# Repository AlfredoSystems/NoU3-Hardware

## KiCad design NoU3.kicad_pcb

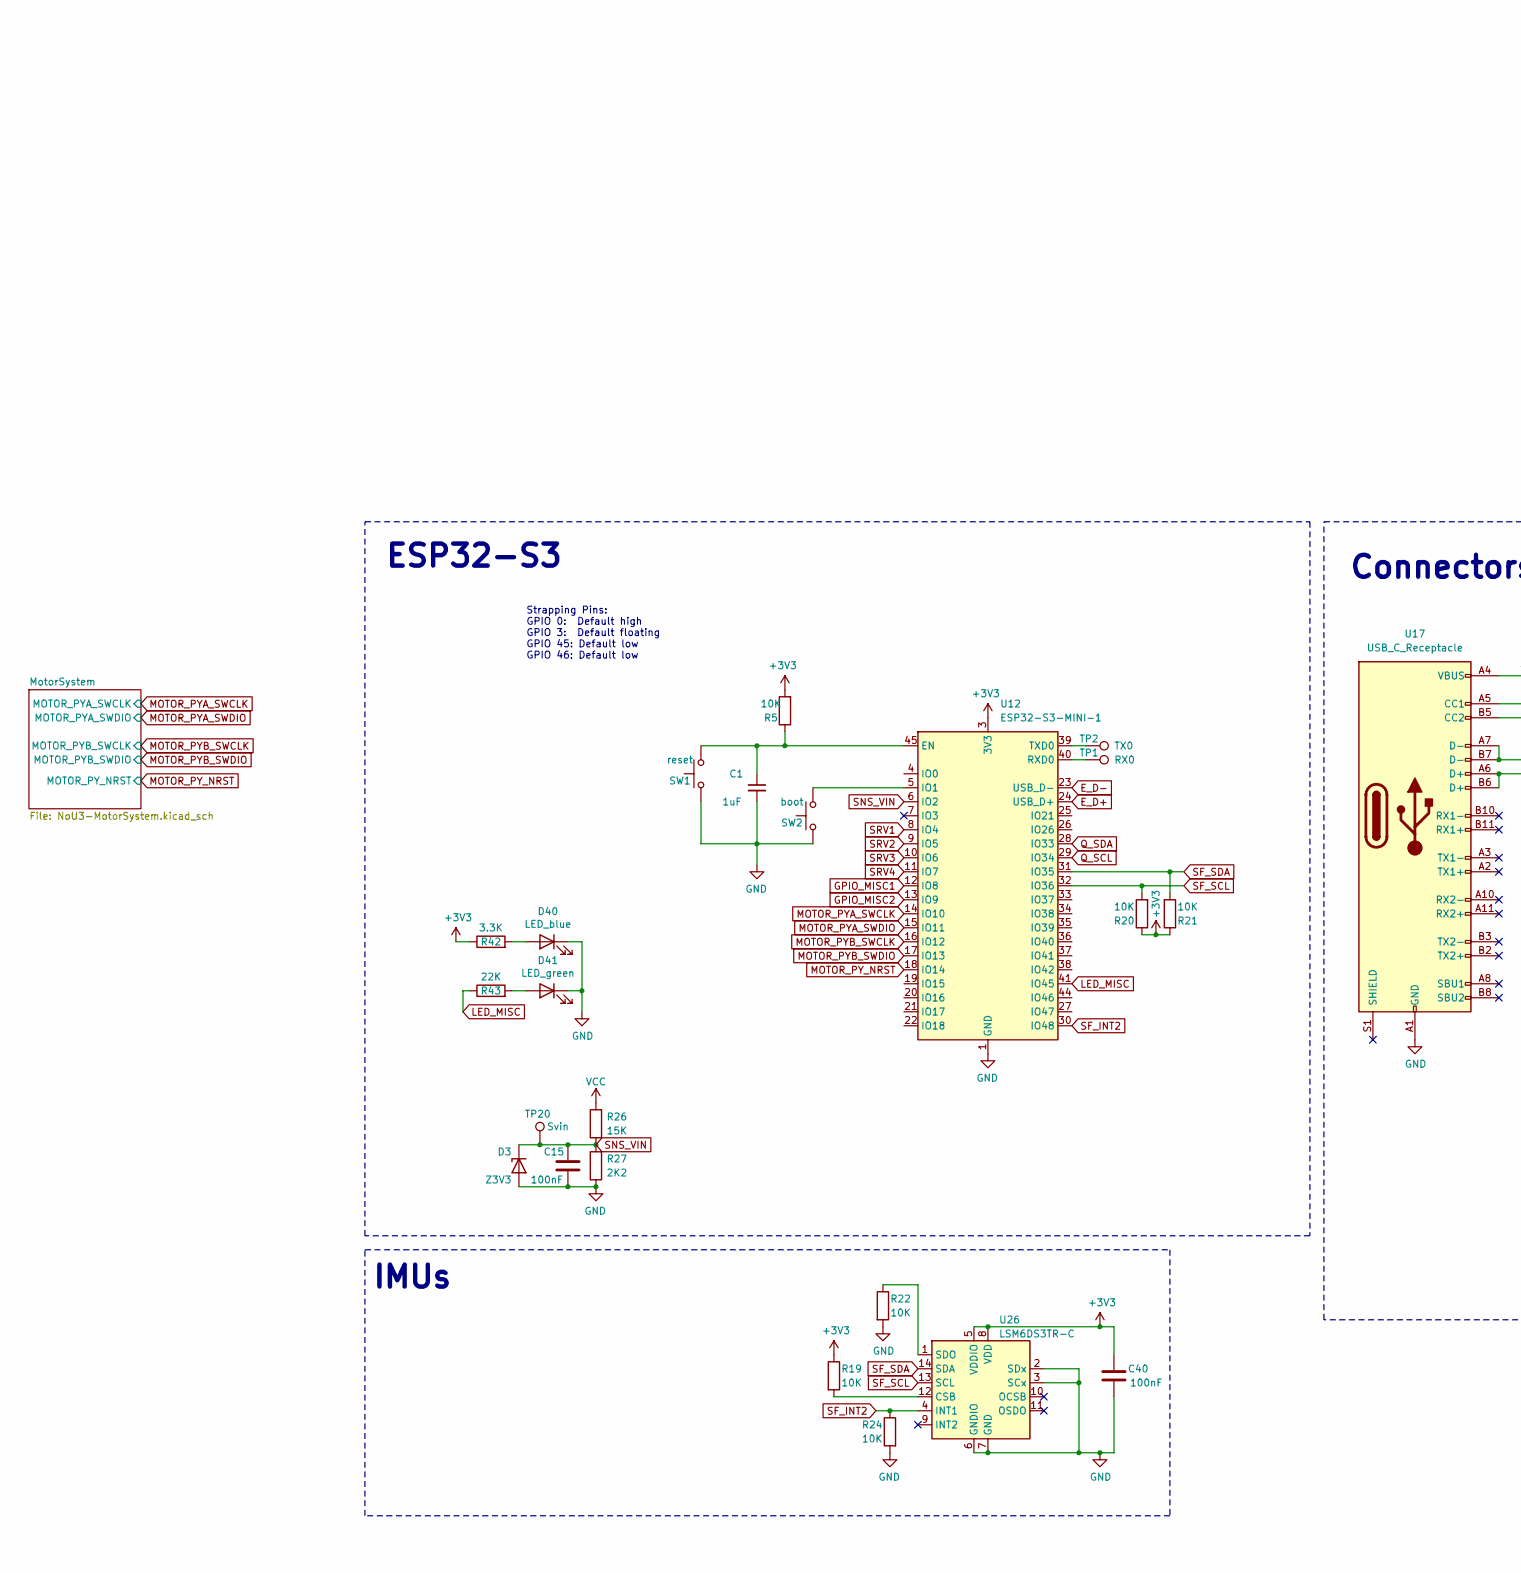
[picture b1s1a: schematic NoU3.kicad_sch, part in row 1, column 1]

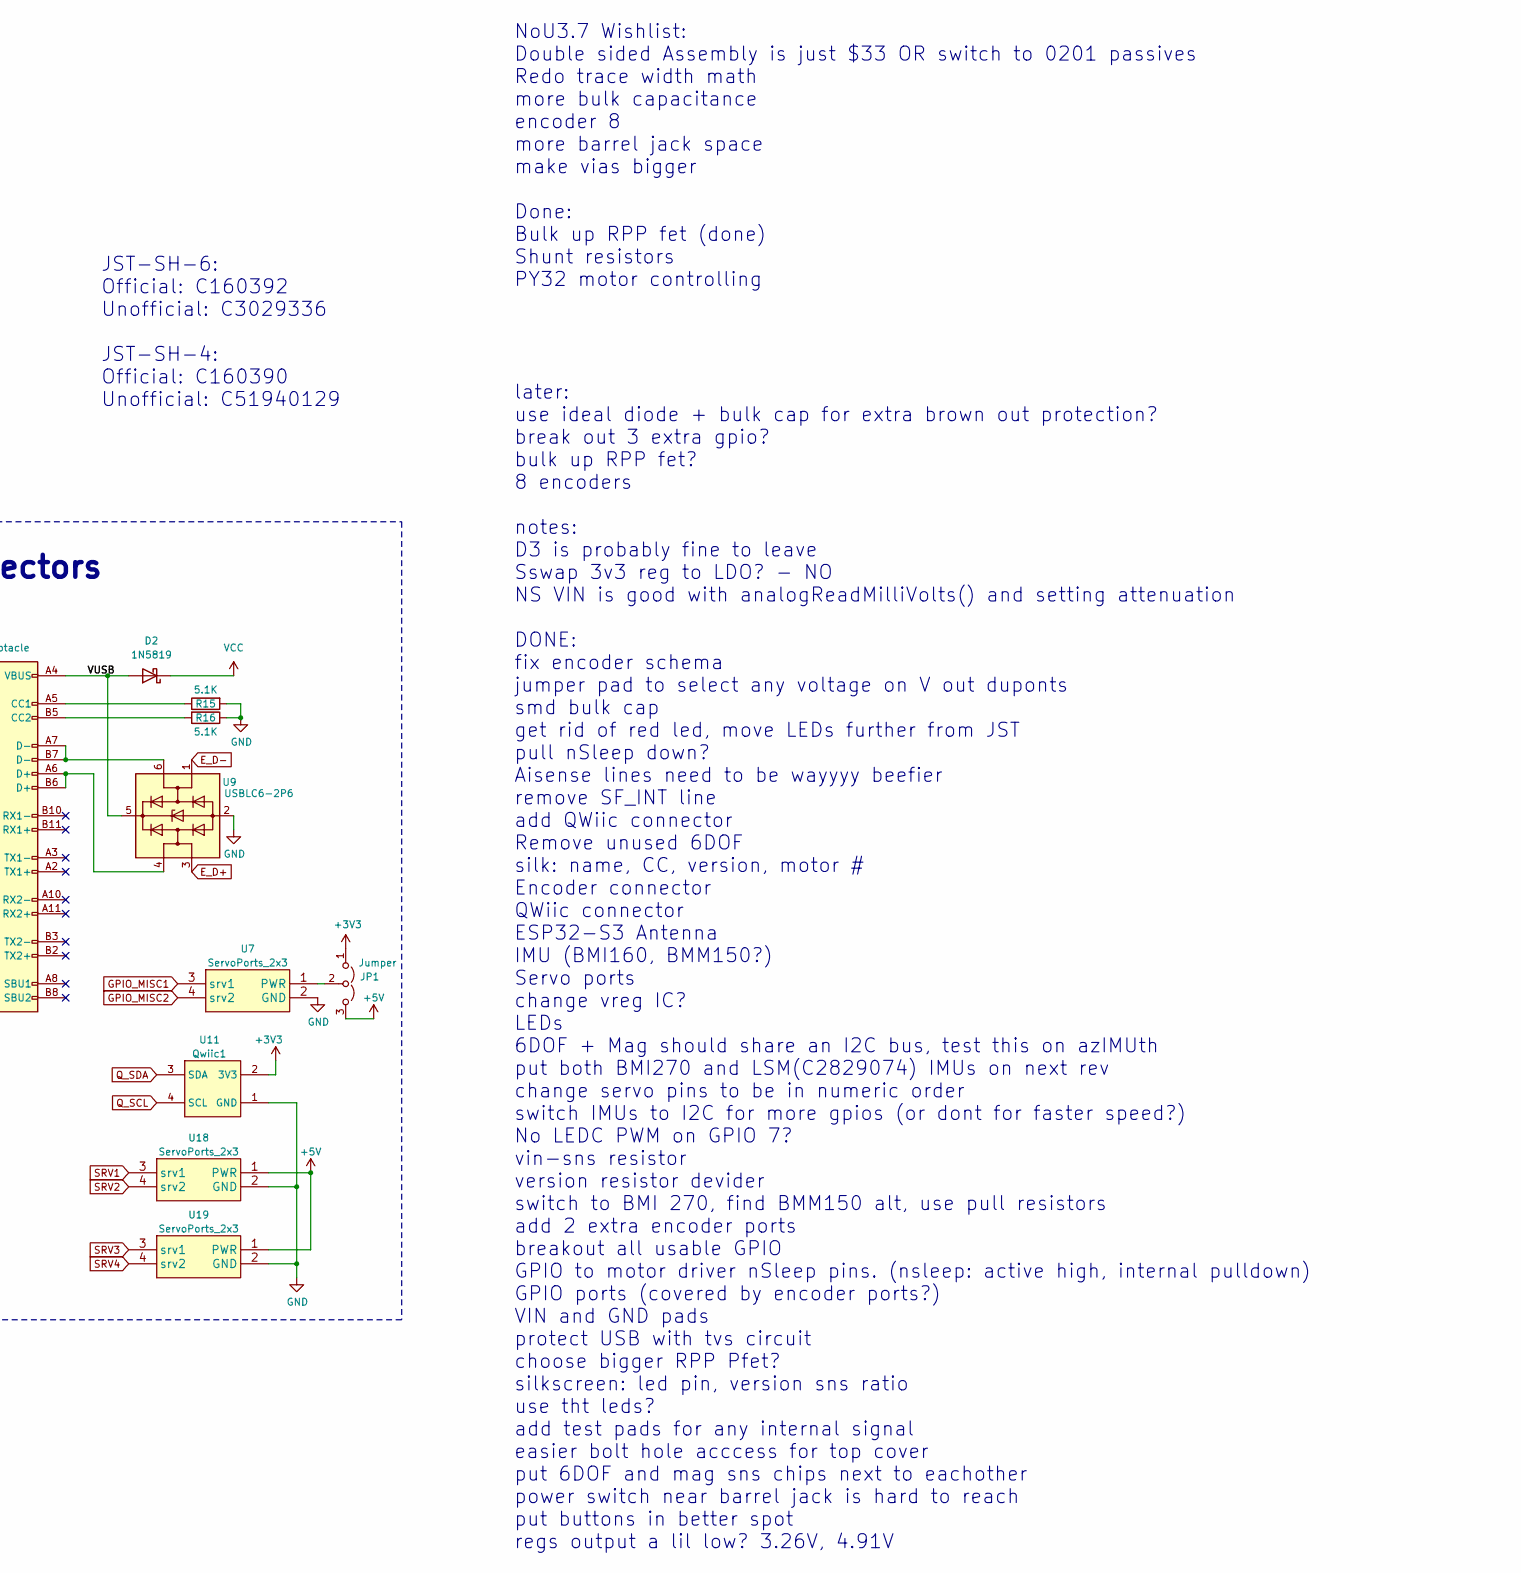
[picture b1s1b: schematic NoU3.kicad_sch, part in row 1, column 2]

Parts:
C1: 1uF; C_0402_1005Metric; LCSC C52923
C15, C40: 100nF; C_0402_1005Metric; LCSC C307331
D2: 1N5819; D_SOD-323; LCSC C191023
D3: Z3V3; D_SOD-323; LCSC C75073
D40: LED_blue; LED_0402_1005Metric; LCSC C130724
D41: LED_green; LED_0402_1005Metric; LCSC C965793
JP1: Jumper; SolderJumper-3-Small
R5, R19, R20, R21, R22, R24: 10K; R_0402_1005Metric; LCSC C25744
R15, R16: 5.1K; R_0402_1005Metric; LCSC C25905
R26: 15K; R_0402_1005Metric; LCSC C25756
R27: 2K2; R_0402_1005Metric; LCSC C25879
R42: 3.3K; R_0402_1005Metric
R43: 22K; R_0402_1005Metric
SW1: reset; Button_SKRKAEE020; LCSC C115357
SW2: boot; Button_SKRKAEE020; LCSC C115357
TP1: RX0; PogoPad1
TP2: TX0; PogoPad1
TP20: Svin; PogoPad1
U7, U18, U19: ServoPorts_2x3; LCSC C5116479
U9: USBLC6-2P6; SOT-666; LCSC C2827693
U11: Qwiic1; JST_SH_BM04B-SRSS-TB_1x04-1MP_P1.00mm_Vertical; LCSC C51940129
U12: ESP32-S3-MINI-1; ESP32-S2-MINI-1; LCSC C2913206
U17: USB_C_Receptacle; USB_TYPE-C-31-M-12; LCSC C165948
U26: LSM6DS3TR-C; Bosch_LGA-14_3x2.5mm_P0.5mm; LCSC C967633

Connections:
+3V3: C40.1, JP1.1 (A), R5.2, R19.1, R20.1, R21.1, R42.1, U11.2 (3V3), U12.3 (3V3), U26.5 (VDDIO), U26.8 (VDD); also elsewhere on the board
+5V: JP1.3 (B), U18.1 (PWR), U19.1 (PWR); also elsewhere on the board
/VUSB: D2.2 (A), U9.5 (VBUS), U17.A4 (VBUS), U17.A9 (VBUS), U17.B4 (VBUS), U17.B9 (VBUS)
E_D+: U9.3 (I/O2), U12.24 (USB_D+)
E_D-: U9.1 (I/O1), U12.23 (USB_D-)
GND: C1.2, C15.2, C40.2, D3.2 (A), D40.1 (K), D41.1 (K), R15.2, R16.1, R22.2, R24.2, R27.1, SW1.2, SW2.2, U7.2 (GND), U9.2 (GND), U11.1 (GND), U12.1 (GND), U12.2 (GND), U12.42 (GND), U12.43 (GND), U12.46 (GND), U12.47 (GND), U12.48 (GND), U12.49 (GND), U12.50 (GND), U12.51 (GND), U12.52 (GND), U12.53 (GND), U12.54 (GND), U12.55 (GND), U12.56 (GND), U12.57 (GND), U12.58 (GND), U12.59 (GND), U12.60 (GND), U12.61 (GND), U12.62 (GND), U12.63 (GND), U12.64 (GND), U12.65 (GND), U17.A1 (GND), U17.A12 (GND), U17.B1 (GND), U17.B12 (GND), U18.2 (GND), U19.2 (GND), U26.2 (SDx), U26.3 (SCx), U26.6 (GNDIO), U26.7 (GND); also elsewhere on the board
GPIO_MISC1: U7.3 (srv1), U12.12 (IO8)
GPIO_MISC2: U7.4 (srv2), U12.13 (IO9)
LED_MISC: R43.1, U12.41 (IO45)
MOTOR_PYA_SWCLK: U12.14 (IO10); also elsewhere on the board
MOTOR_PYA_SWDIO: U12.15 (IO11); also elsewhere on the board
MOTOR_PYB_SWCLK: U12.16 (IO12); also elsewhere on the board
MOTOR_PYB_SWDIO: U12.17 (IO13); also elsewhere on the board
MOTOR_PY_NRST: U12.18 (IO14); also elsewhere on the board
unnamed: D40.2 (A), R42.2
unnamed: D41.2 (A), R43.2
unnamed: JP1.2 (C), U7.1 (PWR)
unnamed: C1.1, R5.1, SW1.1, U12.45 (EN)
unnamed: SW2.1, U12.5 (IO1)
unnamed: TP1.1 (1_1), U12.40 (RXD0)
unnamed: TP2.1 (1_1), U12.39 (TXD0)
unnamed: R15.1, U17.A5 (CC1)
unnamed: R16.2, U17.B5 (CC2)
unnamed: U9.4 (I/O2), U17.A6 (D+), U17.B6 (D+)
unnamed: U9.6 (I/O1), U17.A7 (D-), U17.B7 (D-)
unnamed: R19.2, U26.12 (CSB)
unnamed: R22.1, U26.1 (SDO)
Q_SCL: U11.4 (SCL), U12.29 (IO34)
Q_SDA: U11.3 (SDA), U12.28 (IO33)
SF_INT2: R24.1, U12.30 (IO48), U26.4 (INT1)
SF_SCL: R20.2, U12.32 (IO36), U26.13 (SCL)
SF_SDA: R21.2, U12.31 (IO35), U26.14 (SDA)
SNS_VIN: C15.1, D3.1 (K), R26.1, R27.2, TP20.1 (1_1), U12.6 (IO2)
SRV1: U12.8 (IO4), U18.3 (srv1)
SRV2: U12.9 (IO5), U18.4 (srv2)
SRV3: U12.10 (IO6), U19.3 (srv1)
SRV4: U12.11 (IO7), U19.4 (srv2)
VCC: D2.1 (K), R26.2; also elsewhere on the board

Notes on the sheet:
IMUs
Strapping Pins: GPIO 0: Default high GPIO 3: Default floating GPIO 45: Default low GPIO 46: Default low
NoU3.7 Wishlist: Double sided Assembly is just $33 OR switch to 0201 passives Redo trace width math more bulk capacitance encoder 8 more barrel jack space make vias bigger Done: Bulk up RPP fet (done) Shunt resistors PY32 motor controlling later: use ideal diode + bulk cap for extra brown out prote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
Connectors
ESP32-S3
JST-SH-6: Official: C160392 Unofficial: C3029336 JST-SH-4: Official: C160390 Unofficial: C51940129

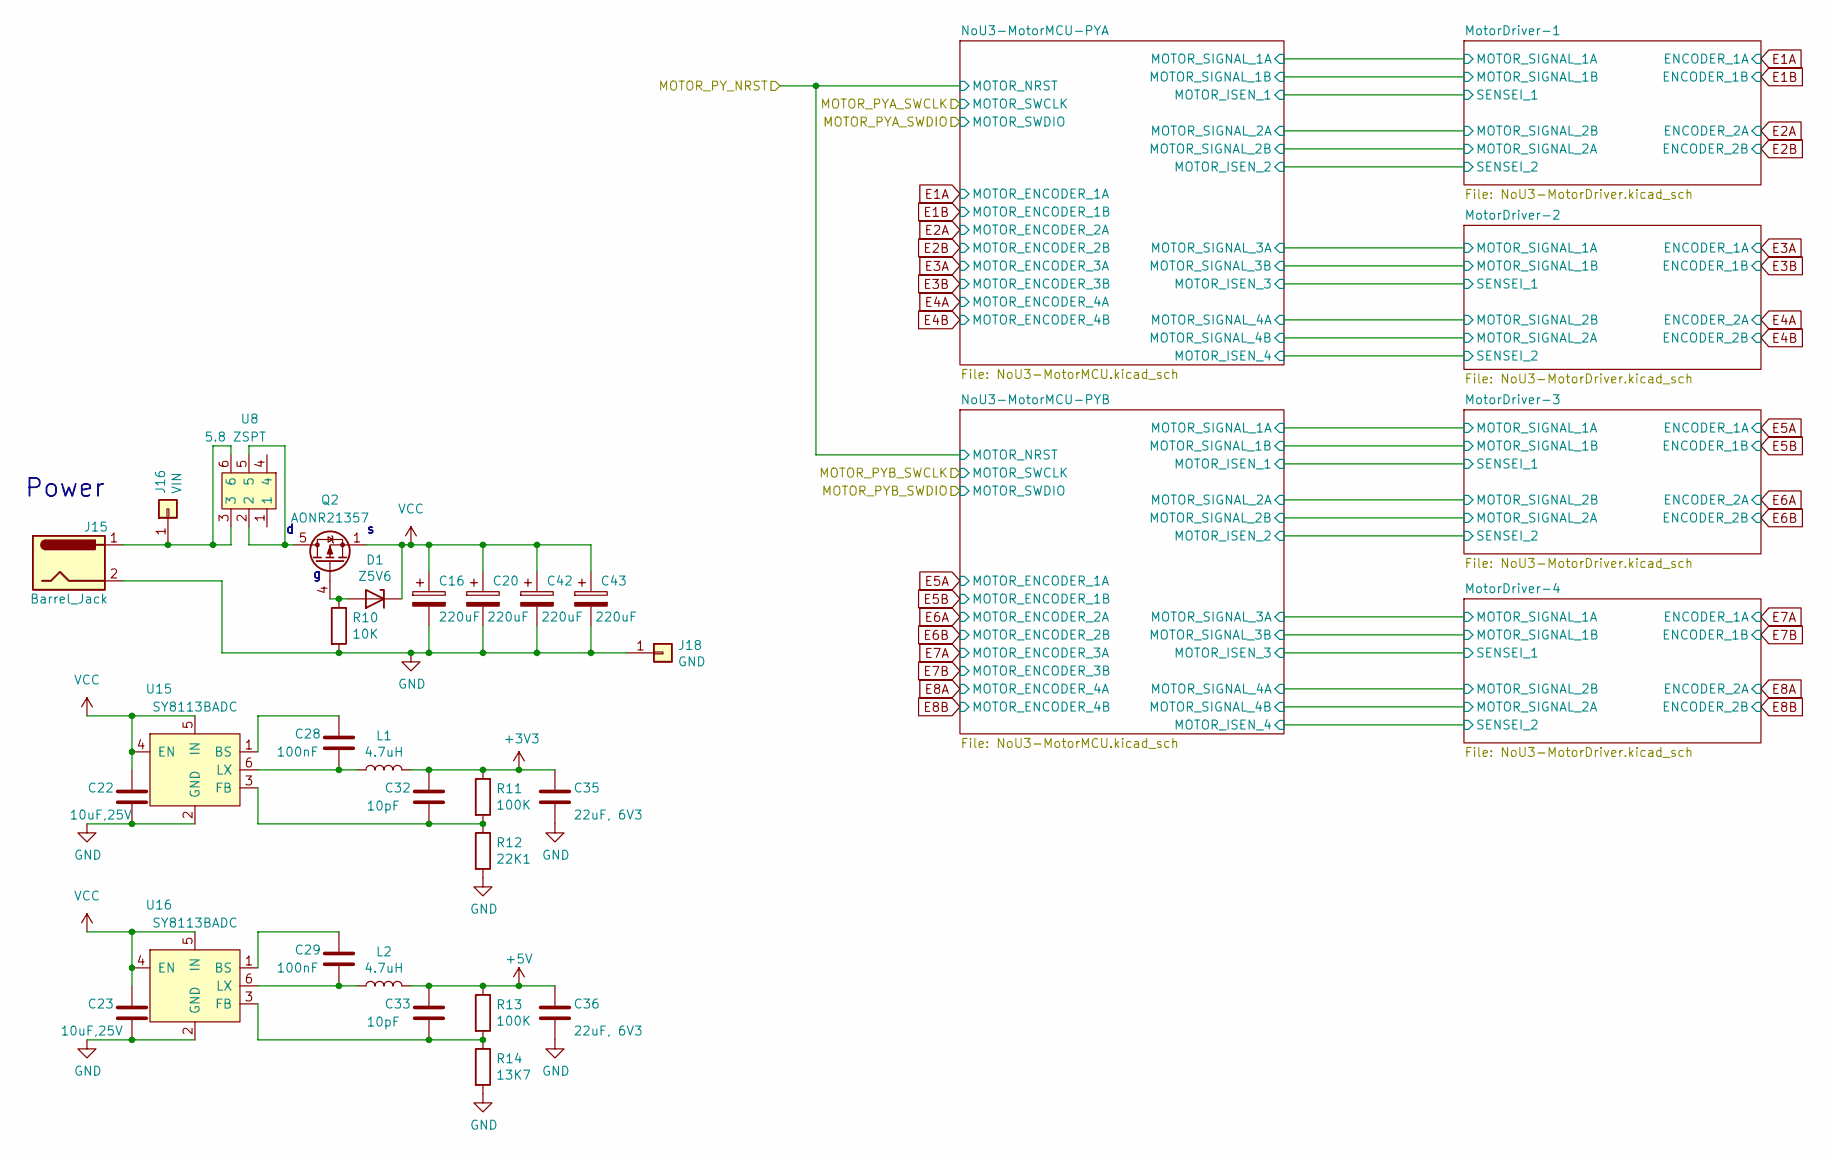
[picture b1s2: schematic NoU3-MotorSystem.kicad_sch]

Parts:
C16, C20, C42, C43: 220uF; CP_Elec_6.3x7.7_slim; LCSC C4747974
C22, C23: 10uF,25V; C_0603_1608Metric; LCSC C96446
C28, C29: 100nF; C_0402_1005Metric; LCSC C307331
C32, C33: 10pF; C_0402_1005Metric; LCSC C32949
C35, C36: 22uF, 6V3; C_0603_1608Metric; LCSC C59461
D1: Z5V6; D_SOD-323; LCSC C22612
J15: Barrel_Jack; DC-005C_1; LCSC C84007
J16: VIN; PinSocket_1x01_P2.54mm_Vertical
J18: GND; PinSocket_1x01_P2.54mm_Vertical
L1, L2: 4.7uH; LVF252A12; LCSC C88528
Q2: AONR21357; DFN-8-1EP_3x3mm_P0.65mm_EP1.55x2.4mm; LCSC C431196
R10: 10K; R_0402_1005Metric; LCSC C25744
R11, R13: 100K; R_0402_1005Metric; LCSC C25741
R12: 22K1; R_0402_1005Metric; LCSC C163478
R14: 13K7; R_0402_1005Metric; LCSC C25854
U8: 5.8 ZSPT; XKB5858-Z-75; LCSC C963201
U15, U16: SY8113BADC; TSOT-23-6; LCSC C78989

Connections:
+3V3: C32.1, C35.1, L1.2, R11.1; also elsewhere on the board
+5V: C33.1, C36.1, L2.2, R13.1; also elsewhere on the board
GND: C16.2, C20.2, C22.2, C23.2, C35.2, C36.2, C42.2, C43.2, J15.2, J18.1 (Pin_1_1), R10.2, R12.2, R14.2, U15.2 (GND), U16.2 (GND); also elsewhere on the board
unnamed: D1.2 (A), Q2.4 (G), R10.1
unnamed: J15.1, J16.1 (Pin_1_1), U8.3, U8.6
unnamed: Q2.5 (D), Q2.6 (D), Q2.7 (D), Q2.8 (D), Q2.9 (D), U8.2, U8.5
unnamed: C28.1, U15.1 (BS)
unnamed: C32.2, R11.2, R12.1, U15.3 (FB)
unnamed: C28.2, L1.1, U15.6 (LX)
unnamed: C29.1, U16.1 (BS)
unnamed: C33.2, R13.2, R14.1, U16.3 (FB)
unnamed: C29.2, L2.1, U16.6 (LX)
VCC: C16.1, C20.1, C22.1, C23.1, C42.1, C43.1, D1.1 (K), Q2.1 (S), Q2.2 (S), Q2.3 (S), U15.4 (EN), U15.5 (IN), U16.4 (EN), U16.5 (IN); also elsewhere on the board

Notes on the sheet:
Power

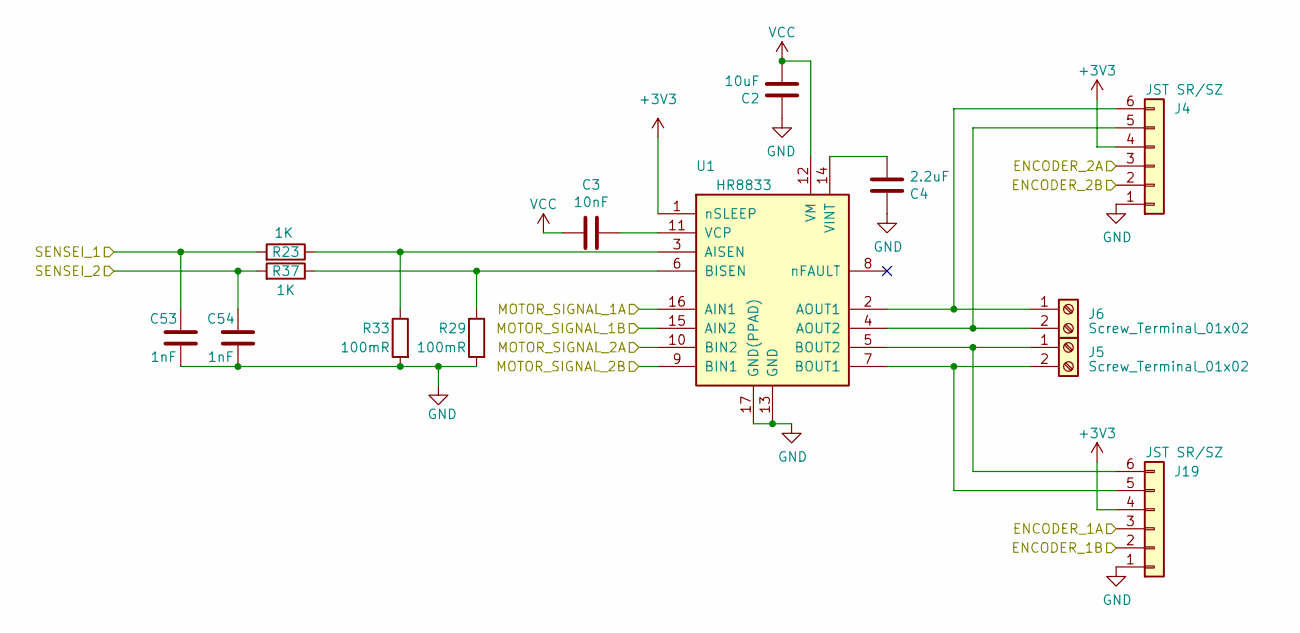
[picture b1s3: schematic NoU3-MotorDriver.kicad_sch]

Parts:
C2: 10uF; C_0805_2012Metric; LCSC C15850
C3: 10nF; C_0402_1005Metric; LCSC C15195
C4: 2.2uF; C_0402_1005Metric; LCSC C12530
C53, C54: 1nF; C_0402_1005Metric; LCSC C1523
J4, J19: JST SR/SZ; JST_SH_1x06_Vertical; LCSC C3029336
J5, J6: Screw_Terminal_01x02; TerminalBlock_Ningbo_2P_5mm; LCSC C557646
R23, R37: 1K; R_0402_1005Metric; LCSC C11702
R29, R33: 100mR; R_0805_2012Metric; LCSC C327057
U1: HR8833; HR8833-0.6mm; LCSC C128666

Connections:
+3V3: J4.4, J19.4, U1.1 (nSLEEP); also elsewhere on the board
/MotorSystem/MotorDriver-1/MOTOR_SIGNAL_1A: U1.16 (AIN1); also elsewhere on the board
/MotorSystem/MotorDriver-1/MOTOR_SIGNAL_1B: U1.15 (AIN2); also elsewhere on the board
/MotorSystem/MotorDriver-1/MOTOR_SIGNAL_2A: U1.10 (BIN2); also elsewhere on the board
/MotorSystem/MotorDriver-1/MOTOR_SIGNAL_2B: U1.9 (BIN1); also elsewhere on the board
/MotorSystem/MotorDriver-1/SENSEI_1: C53.1, R23.2; also elsewhere on the board
/MotorSystem/MotorDriver-1/SENSEI_2: C54.1, R37.2; also elsewhere on the board
E1A: J19.3; also elsewhere on the board
E1B: J19.2; also elsewhere on the board
E2A: J4.3; also elsewhere on the board
E2B: J4.2; also elsewhere on the board
GND: C2.2, C4.2, C53.2, C54.2, J4.1, J19.1, R29.2, R33.2, U1.13 (GND), U1.17 (GND(PPAD)); also elsewhere on the board
unnamed: J4.5, J6.2, U1.4 (AOUT2)
unnamed: J4.6, J6.1, U1.2 (AOUT1)
unnamed: J5.2, J19.5, U1.7 (BOUT1)
unnamed: J5.1, J19.6, U1.5 (BOUT2)
unnamed: R23.1, R33.1, U1.3 (AISEN)
unnamed: R29.1, R37.1, U1.6 (BISEN)
unnamed: C3.2, U1.11 (VCP)
unnamed: C4.1, U1.14 (VINT)
VCC: C2.1, C3.1, U1.12 (VM); also elsewhere on the board

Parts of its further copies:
C5, C8, C11: 10uF; C_0805_2012Metric; LCSC C15850
C6, C9, C12: 10nF; C_0402_1005Metric; LCSC C15195
C7, C10, C13: 2.2uF; C_0402_1005Metric; LCSC C12530
C49, C50, C55, C56, C59, C60: 1nF; C_0402_1005Metric; LCSC C1523
J1, J7, J10, J13, J17, J20: JST SR/SZ; JST_SH_1x06_Vertical; LCSC C3029336
J2, J3, J8, J9, J11, J12: Screw_Terminal_01x02; TerminalBlock_Ningbo_2P_5mm; LCSC C557646
R30, R31, R32, R34, R35, R36: 100mR; R_0805_2012Metric; LCSC C327057
R40, R41, R44, R45, R48, R49: 1K; R_0402_1005Metric; LCSC C11702
U4, U5, U6: HR8833; HR8833-0.6mm; LCSC C128666

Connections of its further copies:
+3V3: J1.4, J7.4, J10.4, J13.4, J17.4, J20.4, U4.1 (nSLEEP), U5.1 (nSLEEP), U6.1 (nSLEEP); also elsewhere on the board
/MotorSystem/MotorDriver-2/MOTOR_SIGNAL_1A: U4.16 (AIN1); also elsewhere on the board
/MotorSystem/MotorDriver-2/MOTOR_SIGNAL_1B: U4.15 (AIN2); also elsewhere on the board
/MotorSystem/MotorDriver-2/MOTOR_SIGNAL_2A: U4.10 (BIN2); also elsewhere on the board
/MotorSystem/MotorDriver-2/MOTOR_SIGNAL_2B: U4.9 (BIN1); also elsewhere on the board
/MotorSystem/MotorDriver-2/SENSEI_1: C55.1, R40.2; also elsewhere on the board
/MotorSystem/MotorDriver-2/SENSEI_2: C56.1, R41.2; also elsewhere on the board
/MotorSystem/MotorDriver-3/MOTOR_SIGNAL_1A: U5.16 (AIN1); also elsewhere on the board
/MotorSystem/MotorDriver-3/MOTOR_SIGNAL_1B: U5.15 (AIN2); also elsewhere on the board
/MotorSystem/MotorDriver-3/MOTOR_SIGNAL_2A: U5.10 (BIN2); also elsewhere on the board
/MotorSystem/MotorDriver-3/MOTOR_SIGNAL_2B: U5.9 (BIN1); also elsewhere on the board
/MotorSystem/MotorDriver-3/SENSEI_1: C49.1, R44.2; also elsewhere on the board
/MotorSystem/MotorDriver-3/SENSEI_2: C50.1, R45.2; also elsewhere on the board
/MotorSystem/MotorDriver-4/MOTOR_SIGNAL_1A: U6.16 (AIN1); also elsewhere on the board
/MotorSystem/MotorDriver-4/MOTOR_SIGNAL_1B: U6.15 (AIN2); also elsewhere on the board
/MotorSystem/MotorDriver-4/MOTOR_SIGNAL_2A: U6.10 (BIN2); also elsewhere on the board
/MotorSystem/MotorDriver-4/MOTOR_SIGNAL_2B: U6.9 (BIN1); also elsewhere on the board
/MotorSystem/MotorDriver-4/SENSEI_1: C59.1, R48.2; also elsewhere on the board
/MotorSystem/MotorDriver-4/SENSEI_2: C60.1, R49.2; also elsewhere on the board
E3A: J7.3; also elsewhere on the board
E3B: J7.2; also elsewhere on the board
E4A: J13.3; also elsewhere on the board
E4B: J13.2; also elsewhere on the board
E5A: J10.3; also elsewhere on the board
E5B: J10.2; also elsewhere on the board
E6A: J17.3; also elsewhere on the board
E6B: J17.2; also elsewhere on the board
E7A: J1.3; also elsewhere on the board
E7B: J1.2; also elsewhere on the board
E8A: J20.3; also elsewhere on the board
E8B: J20.2; also elsewhere on the board
GND: C5.2, C7.2, C8.2, C10.2, C11.2, C13.2, C49.2, C50.2, C55.2, C56.2, C59.2, C60.2, J1.1, J7.1, J10.1, J13.1, J17.1, J20.1, R30.2, R31.2, R32.2, R34.2, R35.2, R36.2, U4.13 (GND), U4.17 (GND(PPAD)), U5.13 (GND), U5.17 (GND(PPAD)), U6.13 (GND), U6.17 (GND(PPAD)); also elsewhere on the board
unnamed: J1.5, J2.2, U6.7 (BOUT1)
unnamed: J1.6, J2.1, U6.5 (BOUT2)
unnamed: J7.5, J8.2, U4.7 (BOUT1)
unnamed: J7.6, J8.1, U4.5 (BOUT2)
unnamed: J10.5, J11.2, U5.7 (BOUT1)
unnamed: J10.6, J11.1, U5.5 (BOUT2)
unnamed: J12.1, J17.6, U5.2 (AOUT1)
unnamed: J12.2, J17.5, U5.4 (AOUT2)
unnamed: J9.2, J13.5, U4.4 (AOUT2)
unnamed: J9.1, J13.6, U4.2 (AOUT1)
unnamed: J3.2, J20.5, U6.4 (AOUT2)
unnamed: J3.1, J20.6, U6.2 (AOUT1)
unnamed: R34.1, R40.1, U4.3 (AISEN)
unnamed: R30.1, R41.1, U4.6 (BISEN)
unnamed: C6.2, U4.11 (VCP)
unnamed: C7.1, U4.14 (VINT)
unnamed: R35.1, R44.1, U5.3 (AISEN)
unnamed: R31.1, R45.1, U5.6 (BISEN)
unnamed: C9.2, U5.11 (VCP)
unnamed: C10.1, U5.14 (VINT)
unnamed: R36.1, R48.1, U6.3 (AISEN)
unnamed: R32.1, R49.1, U6.6 (BISEN)
unnamed: C12.2, U6.11 (VCP)
unnamed: C13.1, U6.14 (VINT)
VCC: C5.1, C6.1, C8.1, C9.1, C11.1, C12.1, U4.12 (VM), U5.12 (VM), U6.12 (VM); also elsewhere on the board

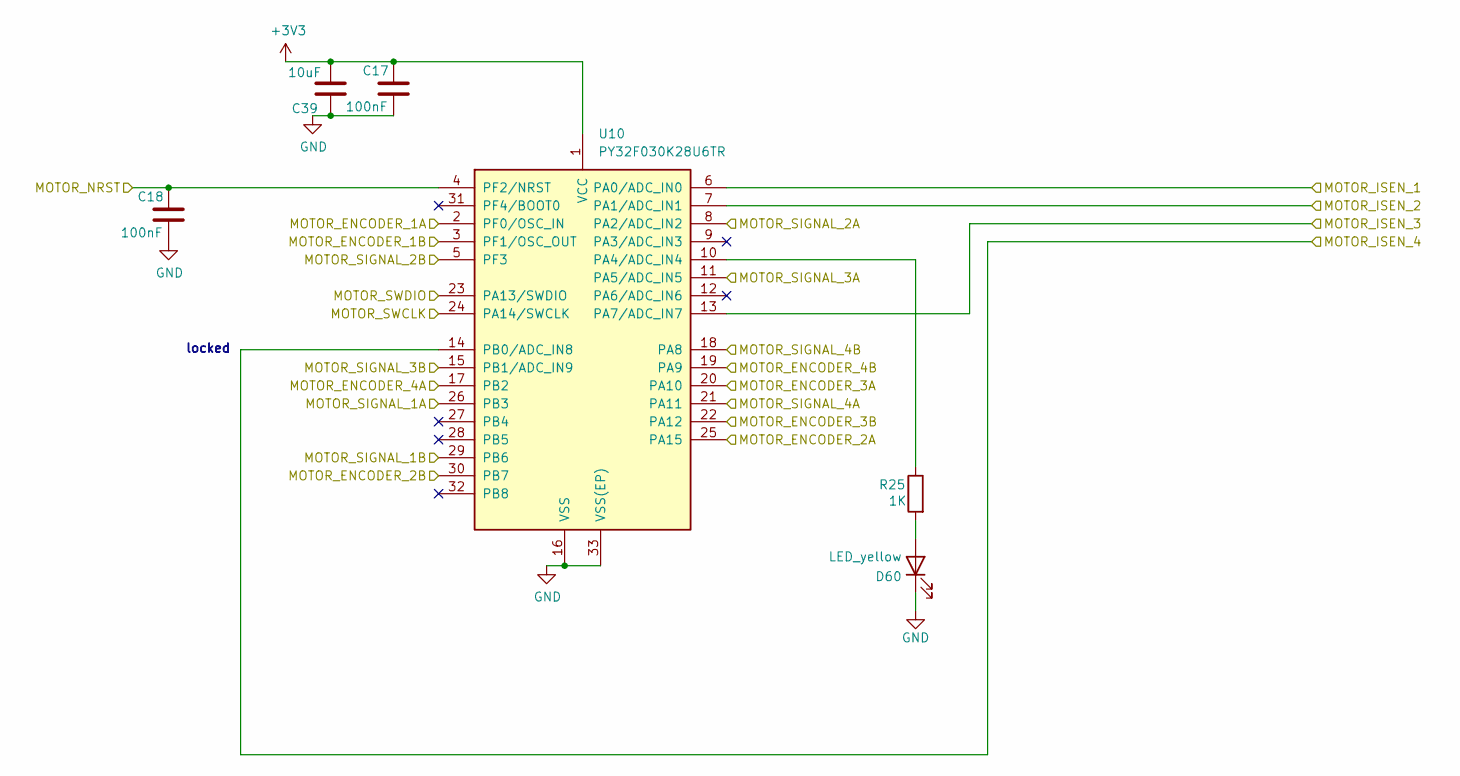
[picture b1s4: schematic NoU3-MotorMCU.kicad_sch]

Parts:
C17, C18: 100nF; C_0402_1005Metric; LCSC C307331
C39: 10uF; C_0402_1005Metric; LCSC C15525
D60: LED_yellow; LED_0402_1005Metric; LCSC C130721
R25: 1K; R_0402_1005Metric; LCSC C11702
U10: PY32F030K28U6TR; VQFN-32-1EP_5x5mm_P0.5mm_EP3.5x3.5mm; LCSC C3018718

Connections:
+3V3: C17.1, C39.2, U10.1 (VCC); also elsewhere on the board
/MotorSystem/MotorDriver-1/MOTOR_SIGNAL_1A: U10.26 (PB3); also elsewhere on the board
/MotorSystem/MotorDriver-1/MOTOR_SIGNAL_1B: U10.29 (PB6); also elsewhere on the board
/MotorSystem/MotorDriver-1/MOTOR_SIGNAL_2A: U10.5 (PF3); also elsewhere on the board
/MotorSystem/MotorDriver-1/MOTOR_SIGNAL_2B: U10.8 (PA2/ADC_IN2); also elsewhere on the board
/MotorSystem/MotorDriver-1/SENSEI_1: U10.6 (PA0/ADC_IN0); also elsewhere on the board
/MotorSystem/MotorDriver-1/SENSEI_2: U10.7 (PA1/ADC_IN1); also elsewhere on the board
/MotorSystem/MotorDriver-2/MOTOR_SIGNAL_1A: U10.11 (PA5/ADC_IN5); also elsewhere on the board
/MotorSystem/MotorDriver-2/MOTOR_SIGNAL_1B: U10.15 (PB1/ADC_IN9); also elsewhere on the board
/MotorSystem/MotorDriver-2/MOTOR_SIGNAL_2A: U10.18 (PA8); also elsewhere on the board
/MotorSystem/MotorDriver-2/MOTOR_SIGNAL_2B: U10.21 (PA11); also elsewhere on the board
/MotorSystem/MotorDriver-2/SENSEI_1: U10.13 (PA7/ADC_IN7); also elsewhere on the board
/MotorSystem/MotorDriver-2/SENSEI_2: U10.14 (PB0/ADC_IN8); also elsewhere on the board
E1A: U10.2 (PF0/OSC_IN); also elsewhere on the board
E1B: U10.3 (PF1/OSC_OUT); also elsewhere on the board
E2A: U10.25 (PA15); also elsewhere on the board
E2B: U10.30 (PB7); also elsewhere on the board
E3A: U10.20 (PA10); also elsewhere on the board
E3B: U10.22 (PA12); also elsewhere on the board
E4A: U10.17 (PB2); also elsewhere on the board
E4B: U10.19 (PA9); also elsewhere on the board
GND: C17.2, C18.2, C39.1, D60.1 (K), U10.16 (VSS), U10.33 (VSS(EP)); also elsewhere on the board
MOTOR_PYA_SWCLK: U10.24 (PA14/SWCLK); also elsewhere on the board
MOTOR_PYA_SWDIO: U10.23 (PA13/SWDIO); also elsewhere on the board
MOTOR_PY_NRST: C18.1, U10.4 (PF2/NRST); also elsewhere on the board
unnamed: D60.2 (A), R25.2
unnamed: R25.1, U10.10 (PA4/ADC_IN4)

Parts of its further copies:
C46, C48: 100nF; C_0402_1005Metric; LCSC C307331
C47: 10uF; C_0402_1005Metric; LCSC C15525
D61: LED_yellow; LED_0402_1005Metric; LCSC C130721
R28: 1K; R_0402_1005Metric; LCSC C11702
U14: PY32F030K28U6TR; VQFN-32-1EP_5x5mm_P0.5mm_EP3.5x3.5mm; LCSC C3018718

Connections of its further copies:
+3V3: C47.2, C48.1, U14.1 (VCC); also elsewhere on the board
/MotorSystem/MotorDriver-3/MOTOR_SIGNAL_1A: U14.26 (PB3); also elsewhere on the board
/MotorSystem/MotorDriver-3/MOTOR_SIGNAL_1B: U14.29 (PB6); also elsewhere on the board
/MotorSystem/MotorDriver-3/MOTOR_SIGNAL_2A: U14.5 (PF3); also elsewhere on the board
/MotorSystem/MotorDriver-3/MOTOR_SIGNAL_2B: U14.8 (PA2/ADC_IN2); also elsewhere on the board
/MotorSystem/MotorDriver-3/SENSEI_1: U14.6 (PA0/ADC_IN0); also elsewhere on the board
/MotorSystem/MotorDriver-3/SENSEI_2: U14.7 (PA1/ADC_IN1); also elsewhere on the board
/MotorSystem/MotorDriver-4/MOTOR_SIGNAL_1A: U14.11 (PA5/ADC_IN5); also elsewhere on the board
/MotorSystem/MotorDriver-4/MOTOR_SIGNAL_1B: U14.15 (PB1/ADC_IN9); also elsewhere on the board
/MotorSystem/MotorDriver-4/MOTOR_SIGNAL_2A: U14.18 (PA8); also elsewhere on the board
/MotorSystem/MotorDriver-4/MOTOR_SIGNAL_2B: U14.21 (PA11); also elsewhere on the board
/MotorSystem/MotorDriver-4/SENSEI_1: U14.13 (PA7/ADC_IN7); also elsewhere on the board
/MotorSystem/MotorDriver-4/SENSEI_2: U14.14 (PB0/ADC_IN8); also elsewhere on the board
E5A: U14.2 (PF0/OSC_IN); also elsewhere on the board
E5B: U14.3 (PF1/OSC_OUT); also elsewhere on the board
E6A: U14.25 (PA15); also elsewhere on the board
E6B: U14.30 (PB7); also elsewhere on the board
E7A: U14.20 (PA10); also elsewhere on the board
E7B: U14.22 (PA12); also elsewhere on the board
E8A: U14.17 (PB2); also elsewhere on the board
E8B: U14.19 (PA9); also elsewhere on the board
GND: C46.2, C47.1, C48.2, D61.1 (K), U14.16 (VSS), U14.33 (VSS(EP)); also elsewhere on the board
MOTOR_PYB_SWCLK: U14.24 (PA14/SWCLK); also elsewhere on the board
MOTOR_PYB_SWDIO: U14.23 (PA13/SWDIO); also elsewhere on the board
MOTOR_PY_NRST: C46.1, U14.4 (PF2/NRST); also elsewhere on the board
unnamed: D61.2 (A), R28.2
unnamed: R28.1, U14.10 (PA4/ADC_IN4)

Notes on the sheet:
locked

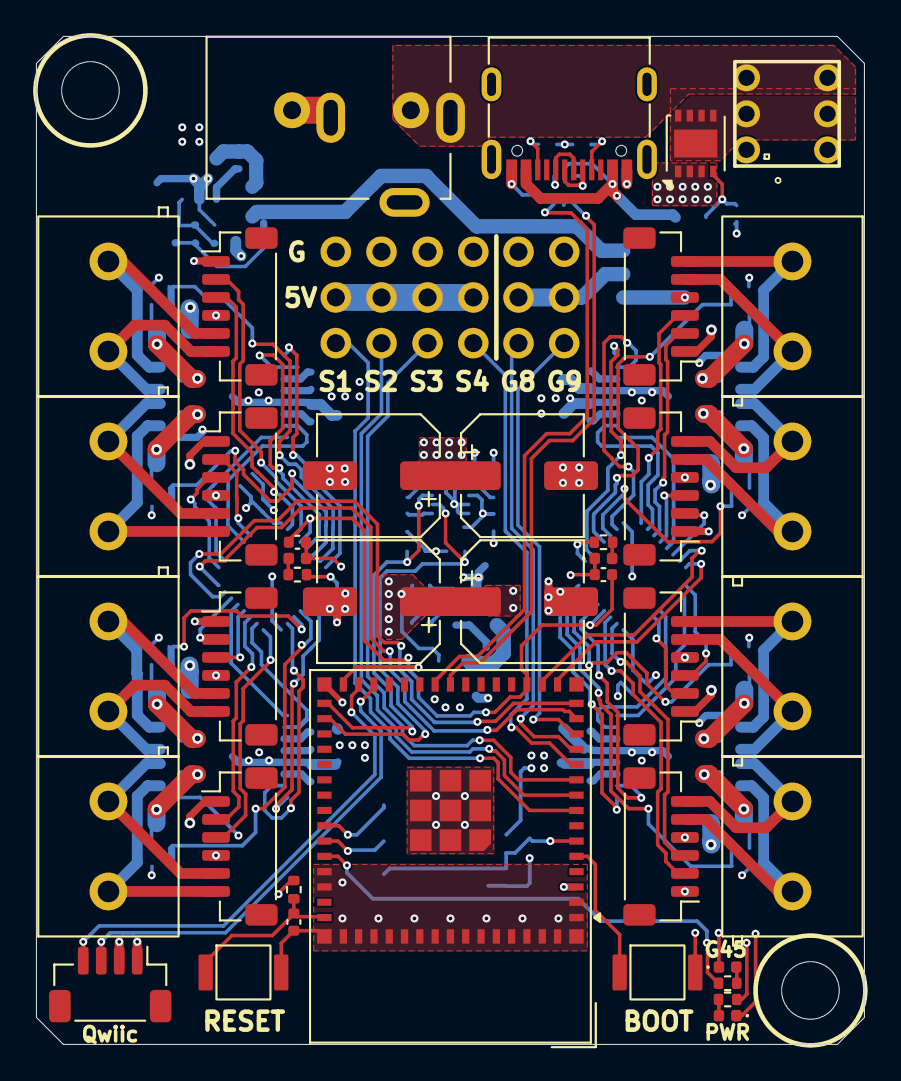
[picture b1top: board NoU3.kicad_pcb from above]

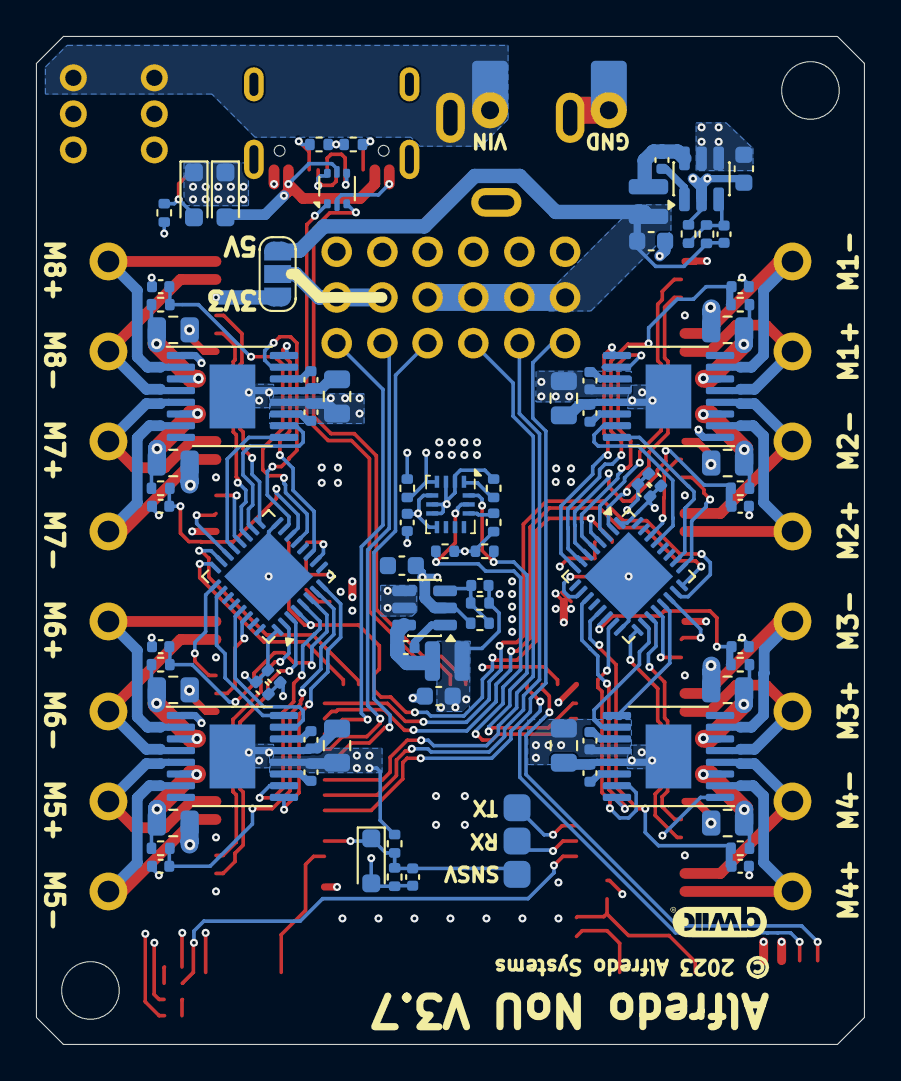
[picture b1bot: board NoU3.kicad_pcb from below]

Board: 4 copper layers, 46.0 x 56.0 mm, 134 parts (85 on the bottom side), 123 nets.

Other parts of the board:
H1, H2: (no value)
TAB1, TAB2, TAB3, TAB4: Tab

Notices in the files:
NoU3-Lite/NoU3-Lite.kicad_pcb:
© 2023 Alfredo Systems
